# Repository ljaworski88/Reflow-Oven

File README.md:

# Reflow-Oven
My take on the diy relfow oven, inspired by the design by Karl Pitrich (karl@pitrich.com).

This reflow oven is still undergoing development, slowly, but works well enough to
bake some ICs. The reflowreader.py program is used to get a graphical output of the 
current temperature and setpoint (you will need to know which serial port the arduino
is connected to), it is written in python 2.7 and will need the correct interpreter.

The door does not open on its own yet and cannot autotune the PID but it can detect
the mains power frequency. The user will need to open the door manually for cooling.
Also fan control has not been implemented as my oven did not have any of that fanciness.

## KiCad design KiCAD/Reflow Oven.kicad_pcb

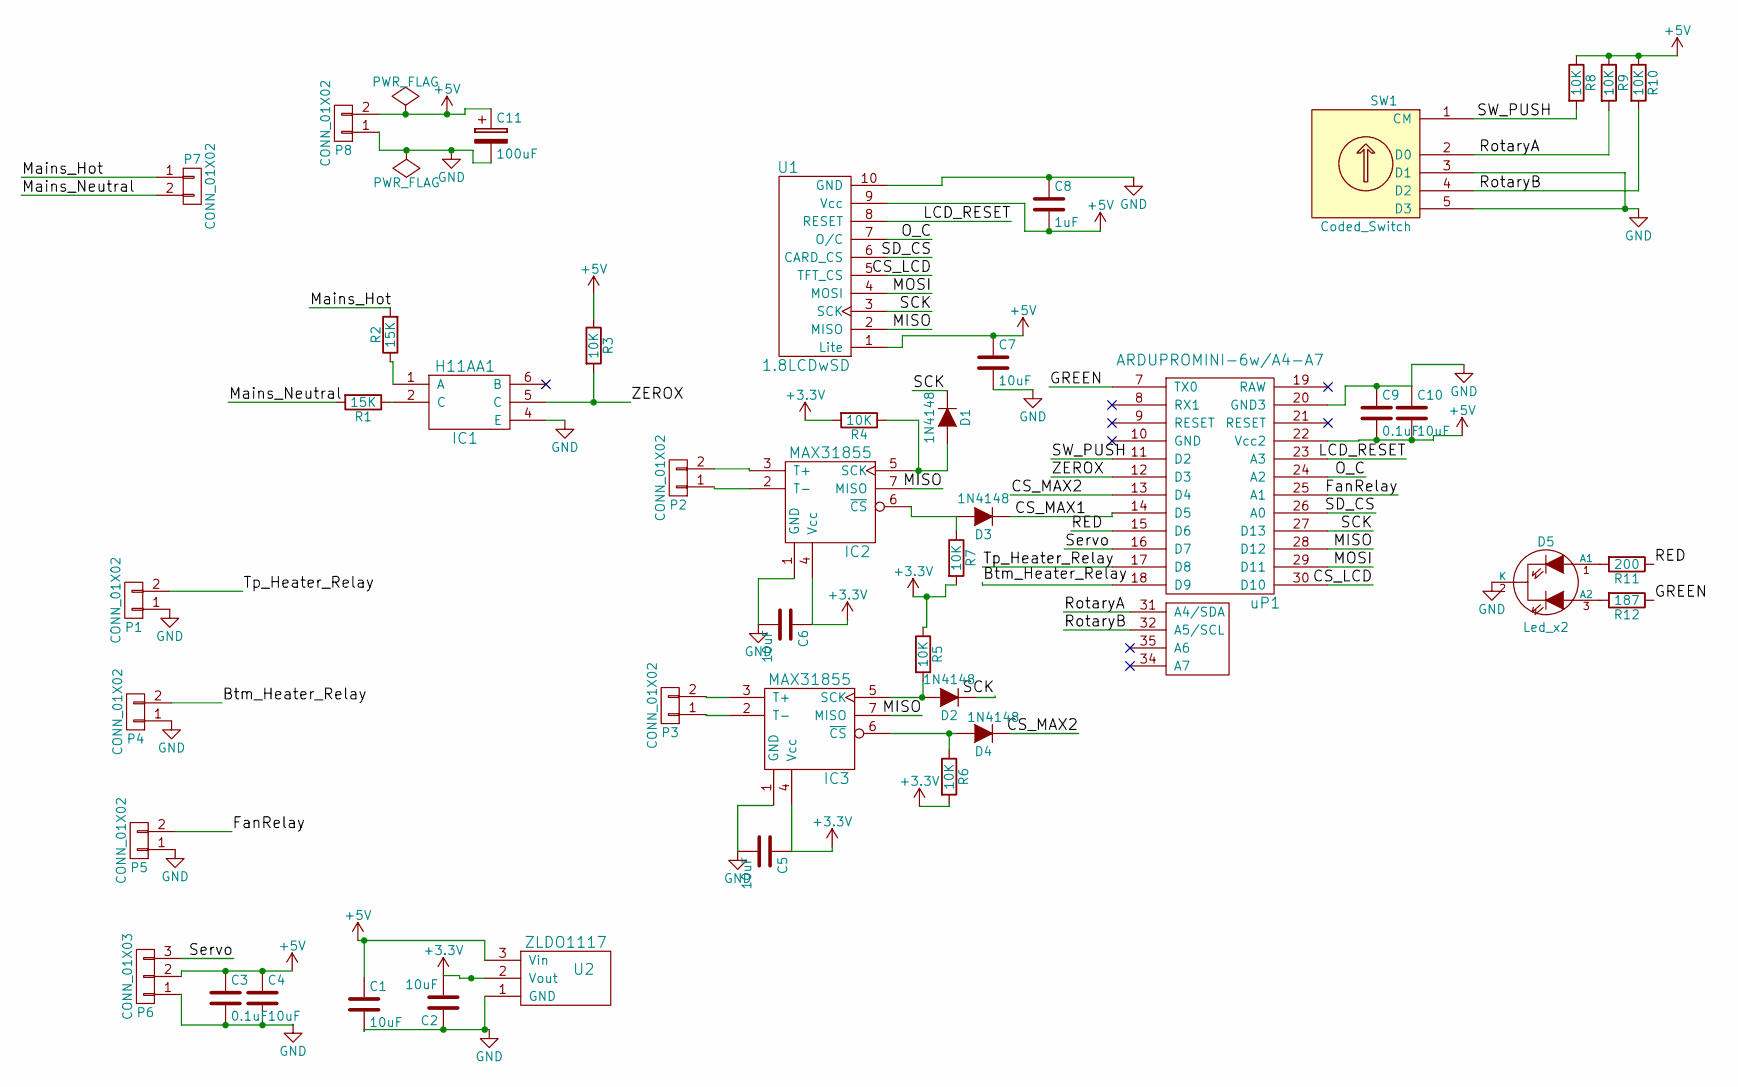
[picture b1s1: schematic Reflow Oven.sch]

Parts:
C1, C2, C4, C5, C6, C7, C10: 10uF; C_0402
C3, C9: 0.1uF; C_0402
C8: 1uF; C_0402
C11: 100uF; 10mm-THRU-ALUMINUM-CAP
D1, D2, D3, D4: 1N4148; SOD-123
D5: Led_x2; LED-5MM-3
IC1: H11AA1; SOIC-6
IC2, IC3: MAX31855; SOIC8
P1, P2, P3, P4, P5, P8: CONN_01X02; TerminalBlock_Pheonix_MPT-2.54mm_2pol
P6: CONN_01X03; SIP3
P7: CONN_01X02; TerminalBlock_Pheonix_PT-3.5mm_2pol
R1, R2: 15K; 1206
R3, R4, R5, R6, R7, R8, R9, R10: 10K; 0402
R11: 200; 0402
R12: 187; 0402
SW1: Coded_Switch; SF-ROTARY-ENCODER
U1: 1.8LCDwSD; 1X10
U2: ZLDO1117; DPAK
uP1: ARDUPROMINI-6w/A4-A7; ArduProMini-6

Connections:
+3V3: C2.2, C5.1, C6.1, IC2.4 (Vcc), IC3.4 (Vcc), R4.2, R5.1, R6.2, R7.2, U2.2 (Vout)
+5V: C1.1, C3.1, C4.1, C7.1, C8.2, C9.2, C10.2, C11.1, P6.2, P8.2, R3.1, R8.1, R9.1, R10.1, U1.1 (Lite), U1.9 (Vcc), U2.3 (Vin), uP1.22 (Vcc2)
/Btm_Heater_Relay: P4.2, uP1.18 (D9)
/CS_LCD: U1.5 (TFT_CS), uP1.30 (D10)
/CS_MAX1: D3.1 (K), uP1.14 (D5)
/CS_MAX2: D4.1 (K), uP1.13 (D4)
/FanRelay: P5.2, uP1.25 (A1)
/GREEN: R12.1, uP1.7 (TX0)
/LCD_RESET: U1.8 (RESET), uP1.23 (A3)
/MISO: IC2.7 (MISO), IC3.7 (MISO), U1.2 (MISO), uP1.28 (D12)
/MOSI: U1.4 (MOSI), uP1.29 (D11)
/Mains_Hot: P7.1, R2.2
/Mains_Neutral: P7.2, R1.2
/O_C: U1.7 (O/C), uP1.24 (A2)
/RED: R11.1, uP1.15 (D6)
/RotaryA: R9.2, SW1.2 (D0), uP1.31 (A4/SDA)
/RotaryB: R10.2, SW1.4 (D2), uP1.32 (A5/SCL)
/SCK: D1.1 (K), D2.1 (K), U1.3 (SCK), uP1.27 (D13)
/SD_CS: U1.6 (CARD_CS), uP1.26 (A0)
/SW_PUSH: R8.2, SW1.1 (CM), uP1.11 (D2)
/Servo: P6.3, uP1.16 (D7)
/Tp_Heater_Relay: P1.2, uP1.17 (D8)
/ZEROX: IC1.5 (C), R3.2, uP1.12 (D3)
GND: C1.2, C2.1, C3.2, C4.2, C5.2, C6.2, C7.2, C8.1, C9.1, C10.1, C11.2, D5.2 (K), IC1.4 (E), IC2.1 (GND), IC3.1 (GND), P1.1, P4.1, P5.1, P6.1, P8.1, SW1.3 (D1), SW1.5 (D3), U1.10 (GND), U2.1 (GND), uP1.20 (GND3)
unnamed: D1.2 (A), IC2.5 (SCK), R4.1
unnamed: D2.2 (A), IC3.5 (SCK), R5.2
unnamed: D3.2 (A), IC2.6 (~CS), R7.1
unnamed: D4.2 (A), IC3.6 (~CS), R6.1
unnamed: D5.1 (A1), R11.2
unnamed: D5.3 (A2), R12.2
unnamed: IC1.1 (A), R2.1
unnamed: IC1.2 (C), R1.1
unnamed: IC2.2 (T-), P2.1
unnamed: IC2.3 (T+), P2.2
unnamed: IC3.2 (T-), P3.1
unnamed: IC3.3 (T+), P3.2

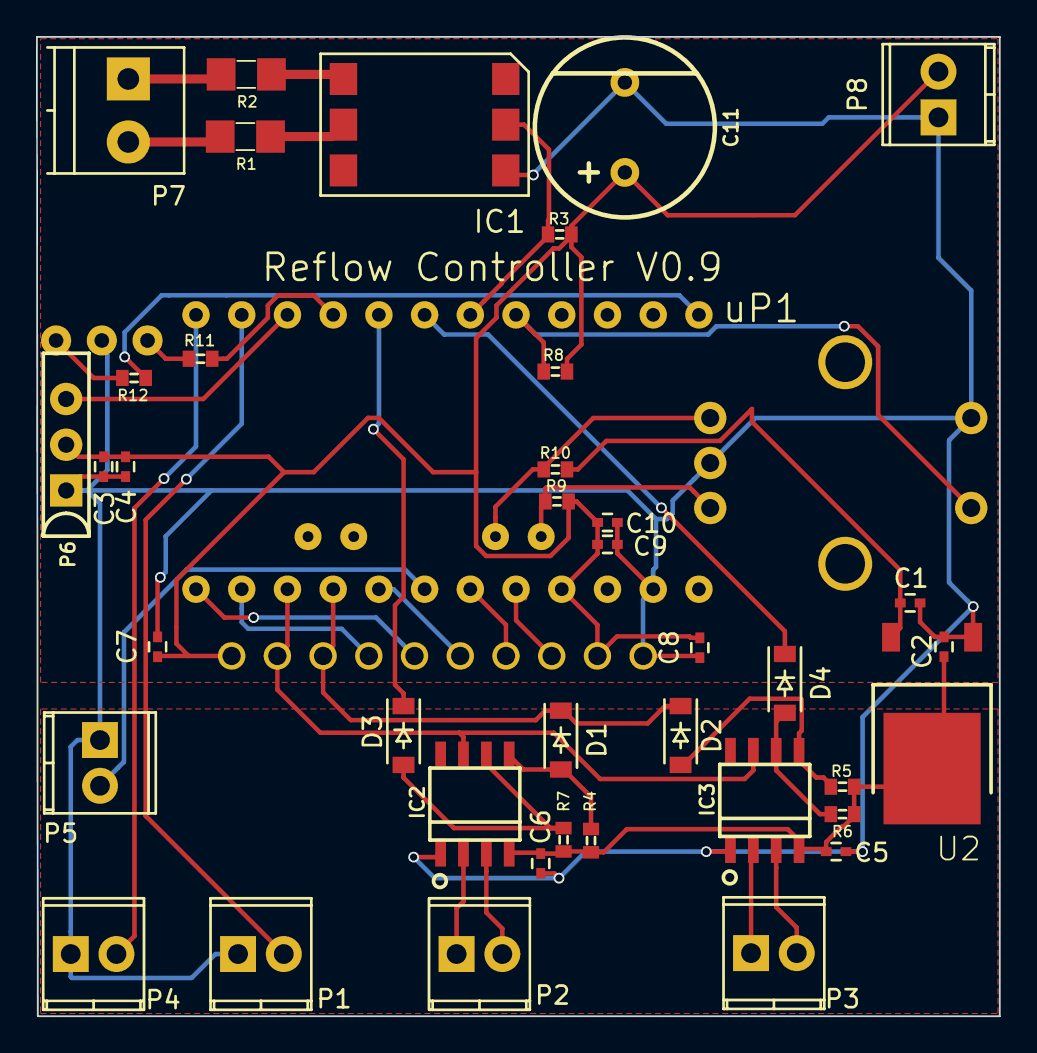
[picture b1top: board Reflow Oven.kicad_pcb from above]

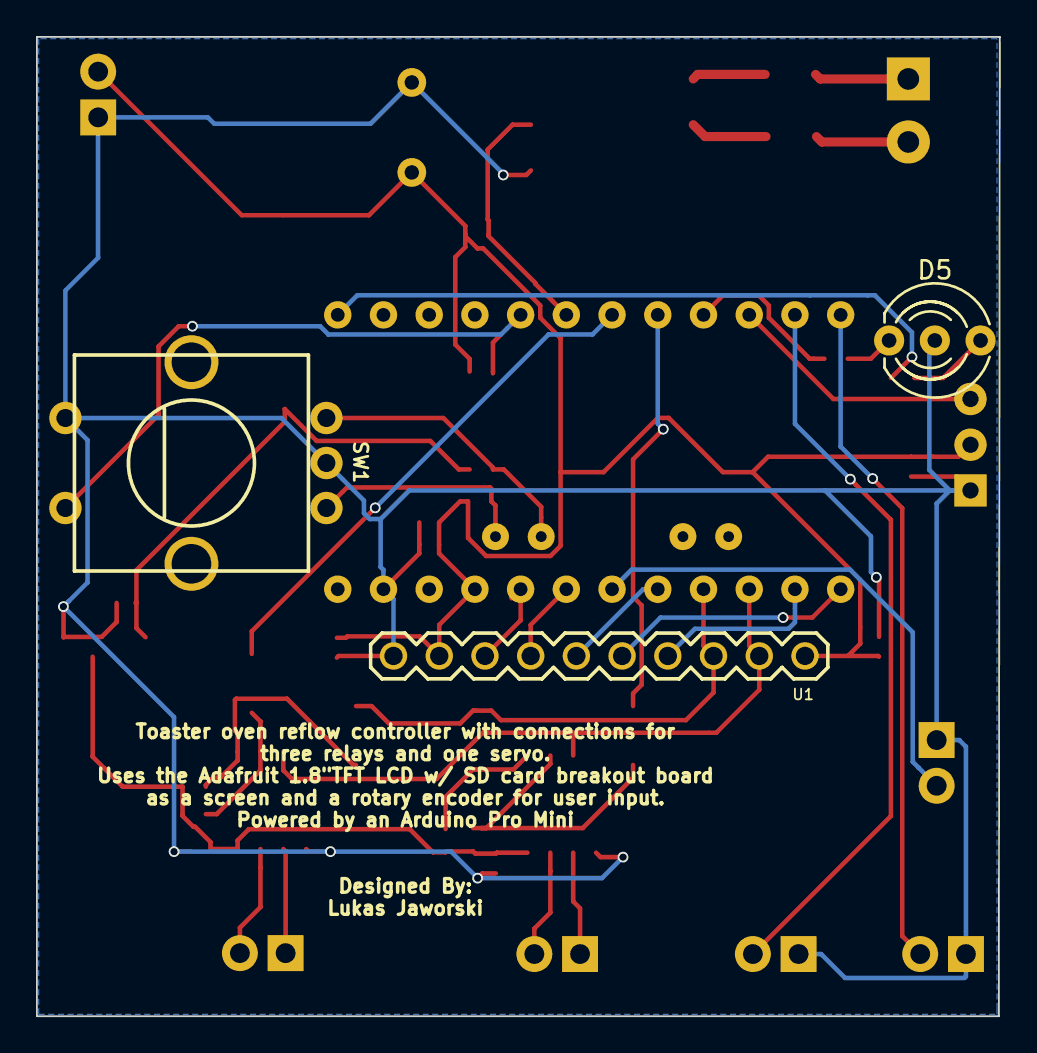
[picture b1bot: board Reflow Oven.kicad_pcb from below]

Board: 2 copper layers, 53.5 x 54.4 mm, 43 parts (3 on the bottom side), 36 nets.

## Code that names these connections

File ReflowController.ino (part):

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#define LCD_CS	10
#define LCD_OC	A2
#define LCD_RST	A3
#define SD_CS	A0


// Thermocouples
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//fan relay &| servo 

#define PIN_FAN		A1// SSR for the fan- This reflow oven has no fan
#define PIN_SERVO	7// servo control signal

// Rotary Encoder

#define ROTARY_A 	A4
#define ROTARY_B	A5
#define SW_PUSH		2

// Zero Crossing Detector

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// volatile uint32_t	zeroXticks = 0; //counts the zero crossing events, used in PID control
uint32_t			lastTimerTicks = 0;
uint32_t			lastPIDticks = 0;//used to ensure that the PID computes every time a heating "cycle" is finnished
uint8_t				usecPerZX = 83;//8.3ms (or 83 ticks @ 100us/tick) between ZeroX for 60Hz mains, 
									//sub in 10 for 50Hz. 
									//This value will be updated if a calibration is performed.
Thermocouple		thermoInput1; //intialize thermocouple 1
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	// digitalWrite(GREEN, LOW);
	pinMode(LCD_CS, OUTPUT);
	digitalWrite(LCD_CS, HIGH);
	pinMode(SD_CS, OUTPUT);
	digitalWrite(SD_CS, HIGH);
	pinMode(LCD_OC, OUTPUT);
	digitalWrite(LCD_OC, LOW);
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	digitalWrite(LCD_RST, LOW);
	pinMode(ROTARY_A, INPUT);
	pinMode(ROTARY_B, INPUT);
	pinMode(SW_PUSH, INPUT);
	doorServo.attach(PIN_SERVO);
}

double initalTemp(rollingAvg& rollAvg, volatile errorCode ErrorCode){//Gets an intial value for the oven temperature
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
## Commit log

2017-01-29 v0.7.2
2017-01-29 v0.7.3
2017-01-29 prepping for larger project merge
2017-01-29 now it does what I want
2017-01-31 adding a bill of materials
2017-01-31 adding files to hopefully be able to finally push this project
2017-01-31 updated the readme
2020-07-29 added license
